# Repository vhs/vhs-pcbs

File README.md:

vhs-pcbs
========

PCB designs from vhs events

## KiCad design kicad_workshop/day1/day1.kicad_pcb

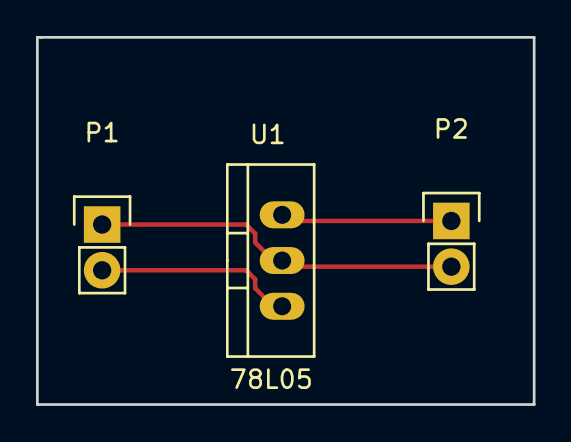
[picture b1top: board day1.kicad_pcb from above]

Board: 2 copper layers, 27.6 x 20.4 mm, 3 parts (0 on the bottom side), 3 nets.

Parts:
P1, P2: CONN_01X02; Pin_Header_Straight_1x02
U1: 78L05; TO-220_Neutral123_Vertical

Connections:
GND: P1.1, P2.2, U1.GND
unnamed: P1.2, U1.VI
unnamed: P2.1, U1.VO

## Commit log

2013-08-16 Eagle files as sent to itead studio
2013-08-16 Files from JohnC
    I've attached the schematic and board files. The parts are from the
    Sparkfun Electronics Eagle libraries here:
    https://github.com/sparkfun/SparkFun-Eagle-Libraries
2013-09-30 Rev A of LED Matrix boards for 5th Anniversary SHHH
2013-09-30 Added BOM and PDF version of schematic
2013-09-30 Added license information
2013-10-29 Signal rename
    Renamed CPLD signals to cpu to reflect reworked hdl code
2013-11-11 Added PNG of bus pirate schematic
2013-11-24 Add bpv3 workshop notes
2013-11-29 Added DXF for acrylic base plate
2014-02-12 Add ethernet gateway from http://kehribar.me/hardware/ethernetGateway/
    Reset/Optiboot still not working. Serial proven, ethernet proven.
2014-02-12 Updated instructions for working ethernet gateway with photos
2014-02-12 Update ethernet gateway reset circuit
2014-02-27 Add rev 0.3 schematic png
2014-03-06 Add first draft of workshop notes
2014-03-14 Updated internet of things photos and notes
2014-03-20 Added usb isolator pcb design
2014-03-20 Updated underside photo to show missing component labels
2014-03-20 Updated internet of things notes
2014-03-27 Added source location to readme
2014-03-27 Fix led orientation in photo
2014-03-27 Add small pcb image
2014-03-27 Cropped small image
2014-03-29 Corrected errors in reset wiring
2014-04-01 Added BOM for usb isolator
2014-04-07 Added markdown parts list and photo
2014-04-07 Tidied parts list, added detail
2014-04-07 removed nreable html parts list
2014-04-15 Ad USB isolator workshop materials
2014-07-26 Add MaKey MaKey materials
2014-07-26 Add MaKeyMaKey readme
2014-07-26 Update MakeyMakey README
2014-09-16 Add RFID door controller code
2014-09-16 Add RFID door opener code
2014-09-23 Added non-blocking serial receive, longer auth string
2015-02-18 Add fet shield pdf
2015-03-04 Updated with 0.2" caps and power switch
2015-03-06 Add GTP for usb-isolator
2015-03-08 Change caps to 0.2 pitch, fix silk issues, panelise into 4 per 10x10 panel
2015-03-17 Maker Faire LED board v2.0 as submitted for proto run
2015-04-26 2015 MF PCB final
2015-04-26 Updaed schematic image
2015-06-29 Add final gerbers
2015-06-29 Added Digikey connector part number from Mike
2015-06-30 Added credit to Mike.
2015-07-30 Adding files from day 1 KiCad workshop
2016-03-21 Added files via upload
    docx file of blinky badge soldering instructions updated for the VHS soldering booth at Maker Faire 2015
2016-03-23 Improve Transistor orientation markings
2016-03-31 Improved transistor marking on overlay
2016-03-31 Added VHS blinky badge photos
    Completed 2015 VHS blinky badges. Designed by Tom K. Used at Maker Faire 2015.
2016-03-31 As sent to seeed studio 2016 Maker Faire
2016-03-31 Reorganised badge files
2016-03-31 Removed obsolete panelised files
2016-10-18 Added missing images
2017-02-01 Updated for 2017 with new domain
2017-02-01 Resolved merge conflict by keeping circle.brd
2017-02-01 Removed duplicate gerbers
2017-02-01 Fixed for 2017 with new domain
2017-02-01 Removed extra file
2017-04-19 Added original arduino leonardo eagle files
2017-04-19 Removed PCB file
2017-04-27 Add copies of sparkfun and adafruit libraries Add FET and PWM output to schematic
2017-04-30 Added DirtyPCBs cam/dru files Added DangerousPrototypes libraries
2017-04-30 Add missing DP files
2017-09-15 Create smd-star-build
2017-09-17 Create smd-star-workshop-docs
2017-09-17 Create derp
2017-09-17 workshop slidedeck, links, and instructions
2018-07-18 led-segment display : updated to rev 1.1 to improve alignment of diagonals and enlarge pads to make hand soldering easier. TODO need an indicator to show top of board to reduce confusion. TODO need t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
